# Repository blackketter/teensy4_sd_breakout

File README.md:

A companion sidecar board with microSD connector to mate with the [Teensy 4 Header Breakout Board](https://github.com/blackketter/teensy4_header_breakout).  It's designed to solder to the top 9 pins on the left side of the header breakout.  The 9th pin provides an optional card detect (short the solder bridge) on digital pin 29.

Designed in KiCad.

Notes:

- See also [Combo SD/USB Host breakout](https://github.com/blackketter/teensy4_combo_breakout)
- In progress: First version works great!
- With longer header pins you should be able to flip the board to be under or over the Teensy 4.0
- Uses [Hirose DM3D microSD socket](https://www.digikey.com/product-detail/en/hirose-electric-co-ltd/DM3D-SF/HR1941CT-ND/1786515)
- Added decoupling cap C1, 0.1uF
- Bridge the CARD DETECT jumper to use pin 29 to detect a card in the slot.  Needs INPUT_PULLUP.

Pinout:

1. 34/SD DAT1
2. 35/SD DAT0
3. GND
4. 36/SD CLK
5. 3.3V
6. 37/SD CMD
7. 38/SD DAT3
8. 39/SD DAT2
9. 29/Card Detect

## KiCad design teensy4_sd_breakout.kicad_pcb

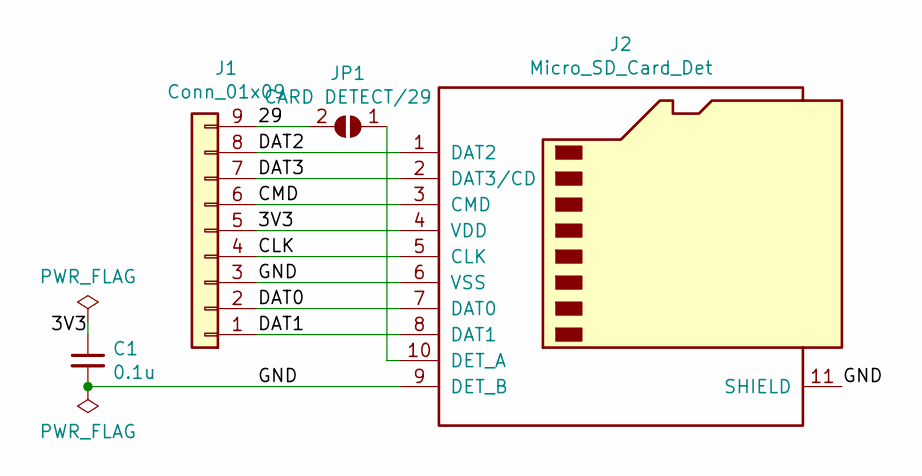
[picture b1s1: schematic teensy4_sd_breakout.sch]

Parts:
C1: 0.1u; C_0805_2012Metric_Pad1.15x1.40mm_HandSolder
J1: Conn_01x09; PinHeader_1x09_P2.54mm_Vertical
J2: Micro_SD_Card_Det; microSD_HC_Hirose_DM3D-SF
JP1: CARD DETECT/29; SolderJumper-2_P1.3mm_Open_RoundedPad1.0x1.5mm

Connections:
/3V3: C1.1, J1.5, J2.4 (VDD)
/29: J1.9, JP1.2 (B)
/CLK: J1.4, J2.5 (CLK)
/CMD: J1.6, J2.3 (CMD)
/DAT0: J1.2, J2.7 (DAT0)
/DAT1: J1.1, J2.8 (DAT1)
/DAT2: J1.8, J2.1 (DAT2)
/DAT3: J1.7, J2.2 (DAT3/CD)
/GND: C1.2, J1.3, J2.6 (VSS), J2.9 (DET_B), J2.11 (SHIELD)
unnamed: J2.10 (DET_A), JP1.1 (A)

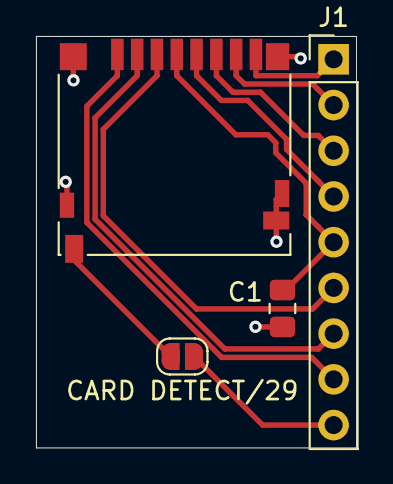
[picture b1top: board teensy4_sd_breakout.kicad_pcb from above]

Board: 2 copper layers, 17.8 x 22.9 mm, 4 parts (0 on the bottom side), 10 nets.

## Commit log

2019-09-20 First pass
2019-09-20 Rename project
2019-09-20 Clarification
2019-09-24 Added decoupling cap and back silk screen
2019-09-24 Document Card Detect pin
2019-10-05 Updated documentation and silkscreen
2019-12-04 Reference combo breakout
